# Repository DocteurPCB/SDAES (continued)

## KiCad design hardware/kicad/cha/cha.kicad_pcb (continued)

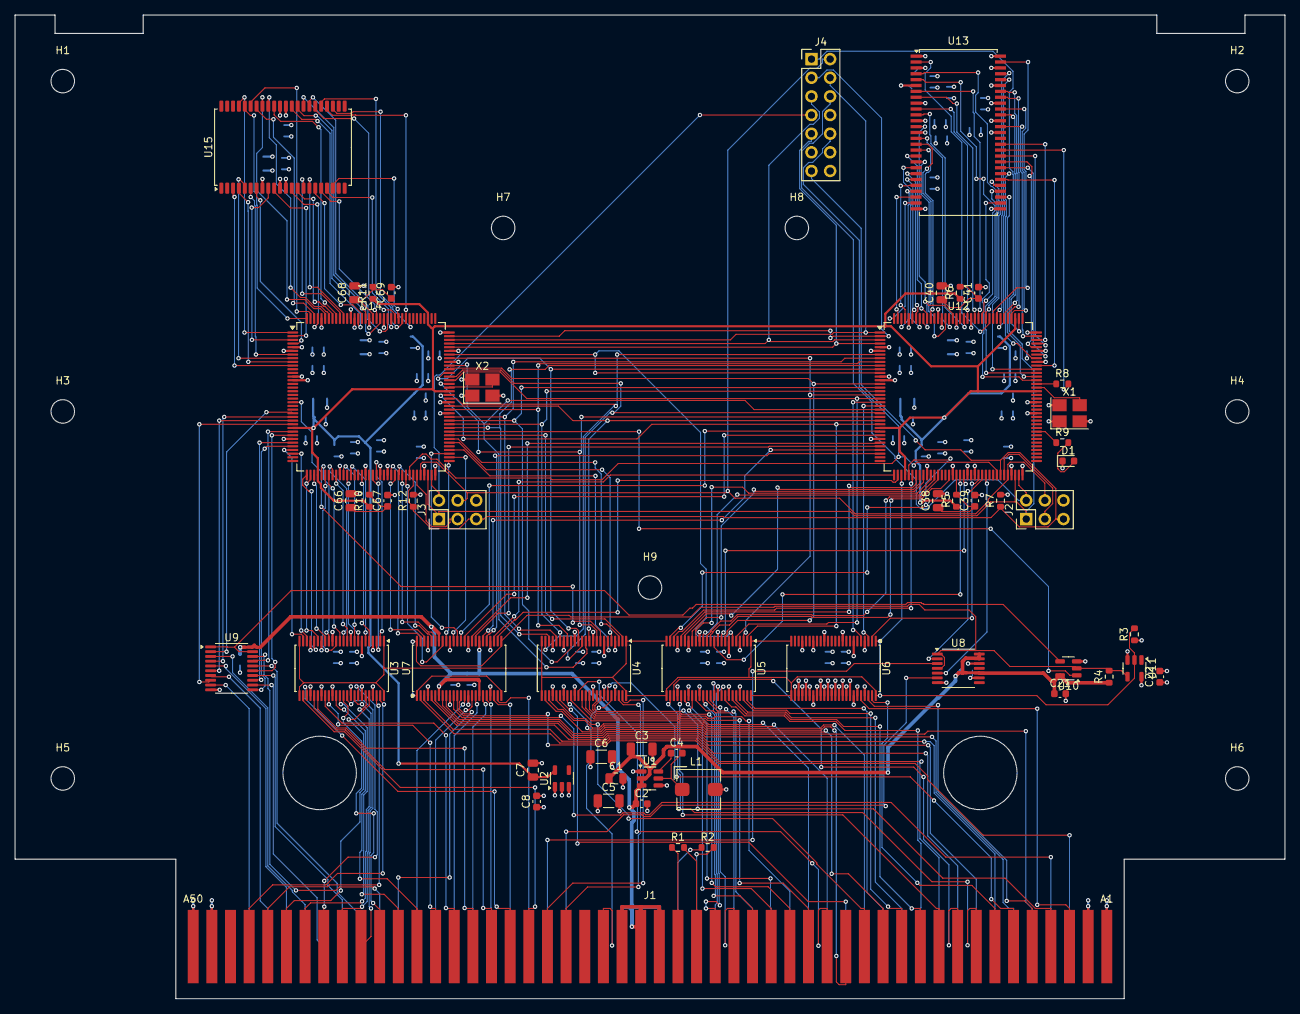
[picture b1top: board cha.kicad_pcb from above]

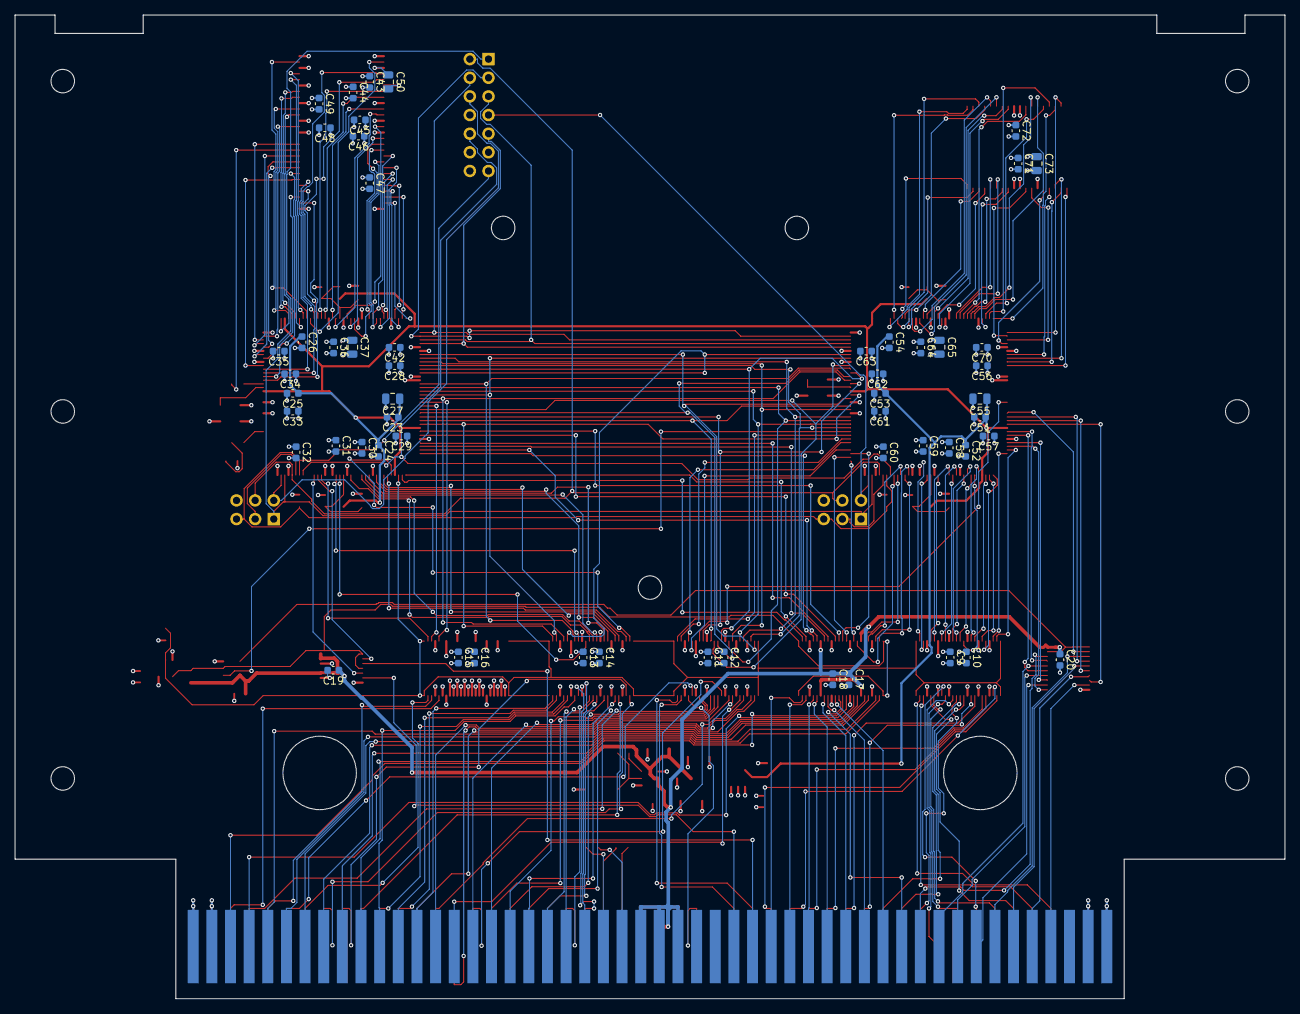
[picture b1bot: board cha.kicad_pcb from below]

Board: 4 copper layers, 173.0 x 134.0 mm, 117 parts (55 on the bottom side), 258 nets.

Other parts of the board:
H1, H2, H3, H4, H5, H6, H7, H8, H9: Entretoise M3; MountingHole_3.2mm_M3

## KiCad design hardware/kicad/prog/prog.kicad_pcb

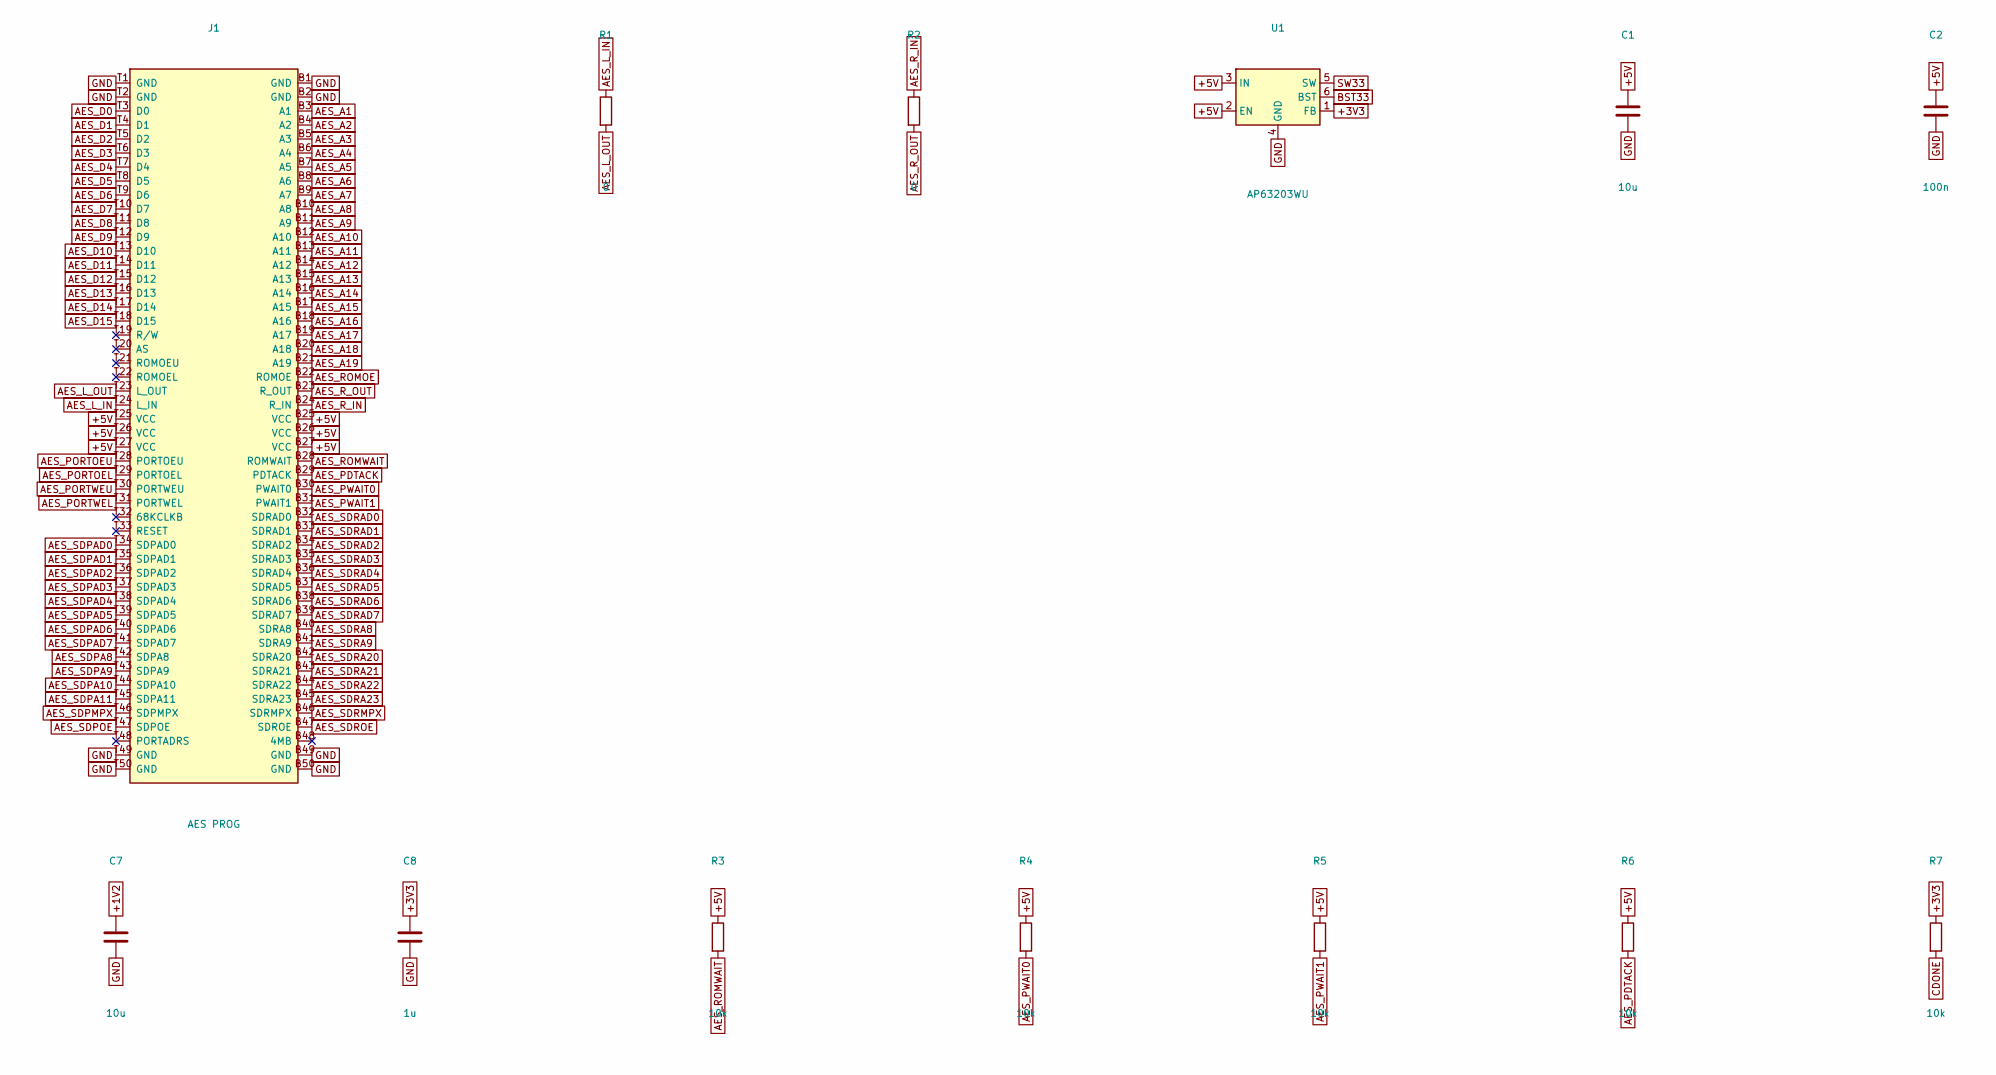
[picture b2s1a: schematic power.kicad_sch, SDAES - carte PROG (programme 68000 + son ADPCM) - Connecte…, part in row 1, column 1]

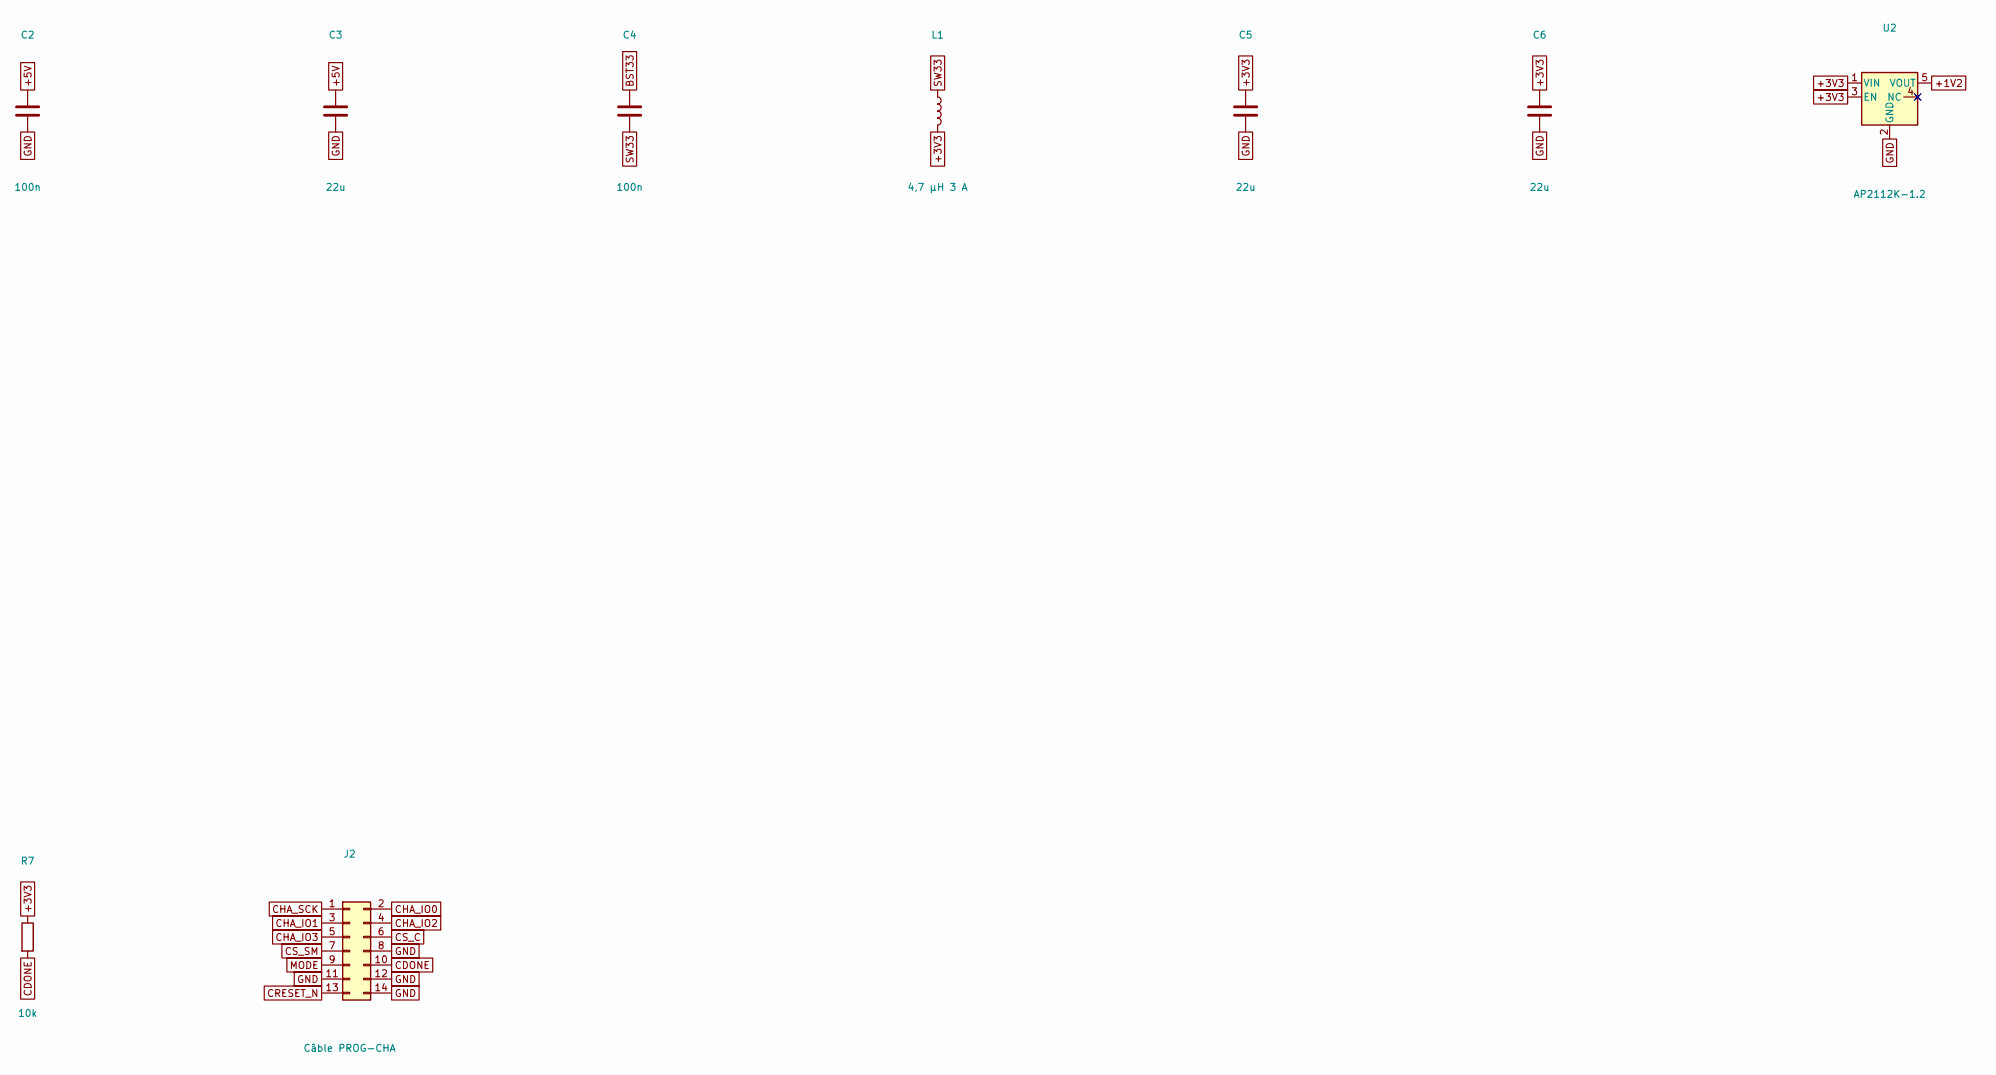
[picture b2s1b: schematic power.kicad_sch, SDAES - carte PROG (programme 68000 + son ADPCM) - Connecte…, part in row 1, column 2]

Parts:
C1, C7: 10u; C_0805_2012Metric
C2, C4: 100n; C_0603_1608Metric
C3, C5, C6: 22u; C_1206_3216Metric
C8: 1u; C_0603_1608Metric
J1: AES PROG; AES_Edge_2x50_P2.54mm
J2: Câble PROG-CHA; PinHeader_2x07_P2.54mm_Vertical
L1: 4,7 µH 3 A; L_Bourns_SRP5030T
R1, R2: 0; R_0603_1608Metric
R3, R4, R5, R6, R7: 10k; R_0603_1608Metric
U1: AP63203WU; TSOT-23-6
U2: AP2112K-1.2; SOT-23-5

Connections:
+1V2: C7.1, U2.5 (VOUT); also elsewhere on the board
+3V3: C5.1, C6.1, C8.1, L1.2, R7.1, U1.1 (FB), U2.1 (VIN), U2.3 (EN); also elsewhere on the board
+5V: C1.1, C2.1, C3.1, J1.B25 (VCC), J1.B26 (VCC), J1.B27 (VCC), J1.T25 (VCC), J1.T26 (VCC), J1.T27 (VCC), R3.1, R4.1, R5.1, R6.1, U1.2 (EN), U1.3 (IN); also elsewhere on the board
AES_A1: J1.B3 (A1); also elsewhere on the board
AES_A2: J1.B4 (A2); also elsewhere on the board
AES_A3: J1.B5 (A3); also elsewhere on the board
AES_A4: J1.B6 (A4); also elsewhere on the board
AES_A5: J1.B7 (A5); also elsewhere on the board
AES_A6: J1.B8 (A6); also elsewhere on the board
AES_A7: J1.B9 (A7); also elsewhere on the board
AES_A8: J1.B10 (A8); also elsewhere on the board
AES_A9: J1.B11 (A9); also elsewhere on the board
AES_A10: J1.B12 (A10); also elsewhere on the board
AES_A11: J1.B13 (A11); also elsewhere on the board
AES_A12: J1.B14 (A12); also elsewhere on the board
AES_A13: J1.B15 (A13); also elsewhere on the board
AES_A14: J1.B16 (A14); also elsewhere on the board
AES_A15: J1.B17 (A15); also elsewhere on the board
AES_A16: J1.B18 (A16); also elsewhere on the board
AES_A17: J1.B19 (A17); also elsewhere on the board
AES_A18: J1.B20 (A18); also elsewhere on the board
AES_A19: J1.B21 (A19); also elsewhere on the board
AES_D0: J1.T3 (D0); also elsewhere on the board
AES_D1: J1.T4 (D1); also elsewhere on the board
AES_D2: J1.T5 (D2); also elsewhere on the board
AES_D3: J1.T6 (D3); also elsewhere on the board
AES_D4: J1.T7 (D4); also elsewhere on the board
AES_D5: J1.T8 (D5); also elsewhere on the board
AES_D6: J1.T9 (D6); also elsewhere on the board
AES_D7: J1.T10 (D7); also elsewhere on the board
AES_D8: J1.T11 (D8); also elsewhere on the board
AES_D9: J1.T12 (D9); also elsewhere on the board
AES_D10: J1.T13 (D10); also elsewhere on the board
AES_D11: J1.T14 (D11); also elsewhere on the board
AES_D12: J1.T15 (D12); also elsewhere on the board
AES_D13: J1.T16 (D13); also elsewhere on the board
AES_D14: J1.T17 (D14); also elsewhere on the board
AES_D15: J1.T18 (D15); also elsewhere on the board
AES_L_IN: J1.T24 (L_IN), R1.1
AES_L_OUT: J1.T23 (L_OUT), R1.2
AES_PDTACK: J1.B29 (PDTACK), R6.2
AES_PORTOEL: J1.T29 (PORTOEL); also elsewhere on the board
AES_PORTOEU: J1.T28 (PORTOEU); also elsewhere on the board
AES_PORTWEL: J1.T31 (PORTWEL); also elsewhere on the board
AES_PORTWEU: J1.T30 (PORTWEU); also elsewhere on the board
AES_PWAIT0: J1.B30 (PWAIT0), R4.2; also elsewhere on the board
AES_PWAIT1: J1.B31 (PWAIT1), R5.2; also elsewhere on the board
AES_ROMOE: J1.B22 (ROMOE); also elsewhere on the board
AES_ROMWAIT: J1.B28 (ROMWAIT), R3.2; also elsewhere on the board
AES_R_IN: J1.B24 (R_IN), R2.1
AES_R_OUT: J1.B23 (R_OUT), R2.2
AES_SDPA8: J1.T42 (SDPA8); also elsewhere on the board
AES_SDPA9: J1.T43 (SDPA9); also elsewhere on the board
AES_SDPA10: J1.T44 (SDPA10); also elsewhere on the board
AES_SDPA11: J1.T45 (SDPA11); also elsewhere on the board
AES_SDPAD0: J1.T34 (SDPAD0); also elsewhere on the board
AES_SDPAD1: J1.T35 (SDPAD1); also elsewhere on the board
AES_SDPAD2: J1.T36 (SDPAD2); also elsewhere on the board
AES_SDPAD3: J1.T37 (SDPAD3); also elsewhere on the board
AES_SDPAD4: J1.T38 (SDPAD4); also elsewhere on the board
AES_SDPAD5: J1.T39 (SDPAD5); also elsewhere on the board
AES_SDPAD6: J1.T40 (SDPAD6); also elsewhere on the board
AES_SDPAD7: J1.T41 (SDPAD7); also elsewhere on the board
AES_SDPMPX: J1.T46 (SDPMPX); also elsewhere on the board
AES_SDPOE: J1.T47 (SDPOE); also elsewhere on the board
AES_SDRA8: J1.B40 (SDRA8); also elsewhere on the board
AES_SDRA9: J1.B41 (SDRA9); also elsewhere on the board
AES_SDRA20: J1.B42 (SDRA20); also elsewhere on the board
AES_SDRA21: J1.B43 (SDRA21); also elsewhere on the board
AES_SDRA22: J1.B44 (SDRA22); also elsewhere on the board
AES_SDRA23: J1.B45 (SDRA23); also elsewhere on the board
AES_SDRAD0: J1.B32 (SDRAD0); also elsewhere on the board
AES_SDRAD1: J1.B33 (SDRAD1); also elsewhere on the board
AES_SDRAD2: J1.B34 (SDRAD2); also elsewhere on the board
AES_SDRAD3: J1.B35 (SDRAD3); also elsewhere on the board
AES_SDRAD4: J1.B36 (SDRAD4); also elsewhere on the board
AES_SDRAD5: J1.B37 (SDRAD5); also elsewhere on the board
AES_SDRAD6: J1.B38 (SDRAD6); also elsewhere on the board
AES_SDRAD7: J1.B39 (SDRAD7); also elsewhere on the board
AES_SDRMPX: J1.B46 (SDRMPX); also elsewhere on the board
AES_SDROE: J1.B47 (SDROE); also elsewhere on the board
BST33: C4.1, U1.6 (BST)
CDONE: J2.10, R7.2; also elsewhere on the board
CHA_IO0: J2.2; also elsewhere on the board
CHA_IO1: J2.3; also elsewhere on the board
CHA_IO2: J2.4; also elsewhere on the board
CHA_IO3: J2.5; also elsewhere on the board
CHA_SCK: J2.1; also elsewhere on the board
CRESET_N: J2.13; also elsewhere on the board
CS_C: J2.6; also elsewhere on the board
CS_SM: J2.7; also elsewhere on the board
GND: C1.2, C2.2, C3.2, C5.2, C6.2, C7.2, C8.2, J1.B1 (GND), J1.B2 (GND), J1.B49 (GND), J1.B50 (GND), J1.T1 (GND), J1.T2 (GND), J1.T49 (GND), J1.T50 (GND), J2.8, J2.11, J2.12, J2.14, U1.4 (GND), U2.2 (GND); also elsewhere on the board
MODE: J2.9; also elsewhere on the board
SW33: C4.2, L1.1, U1.5 (SW)

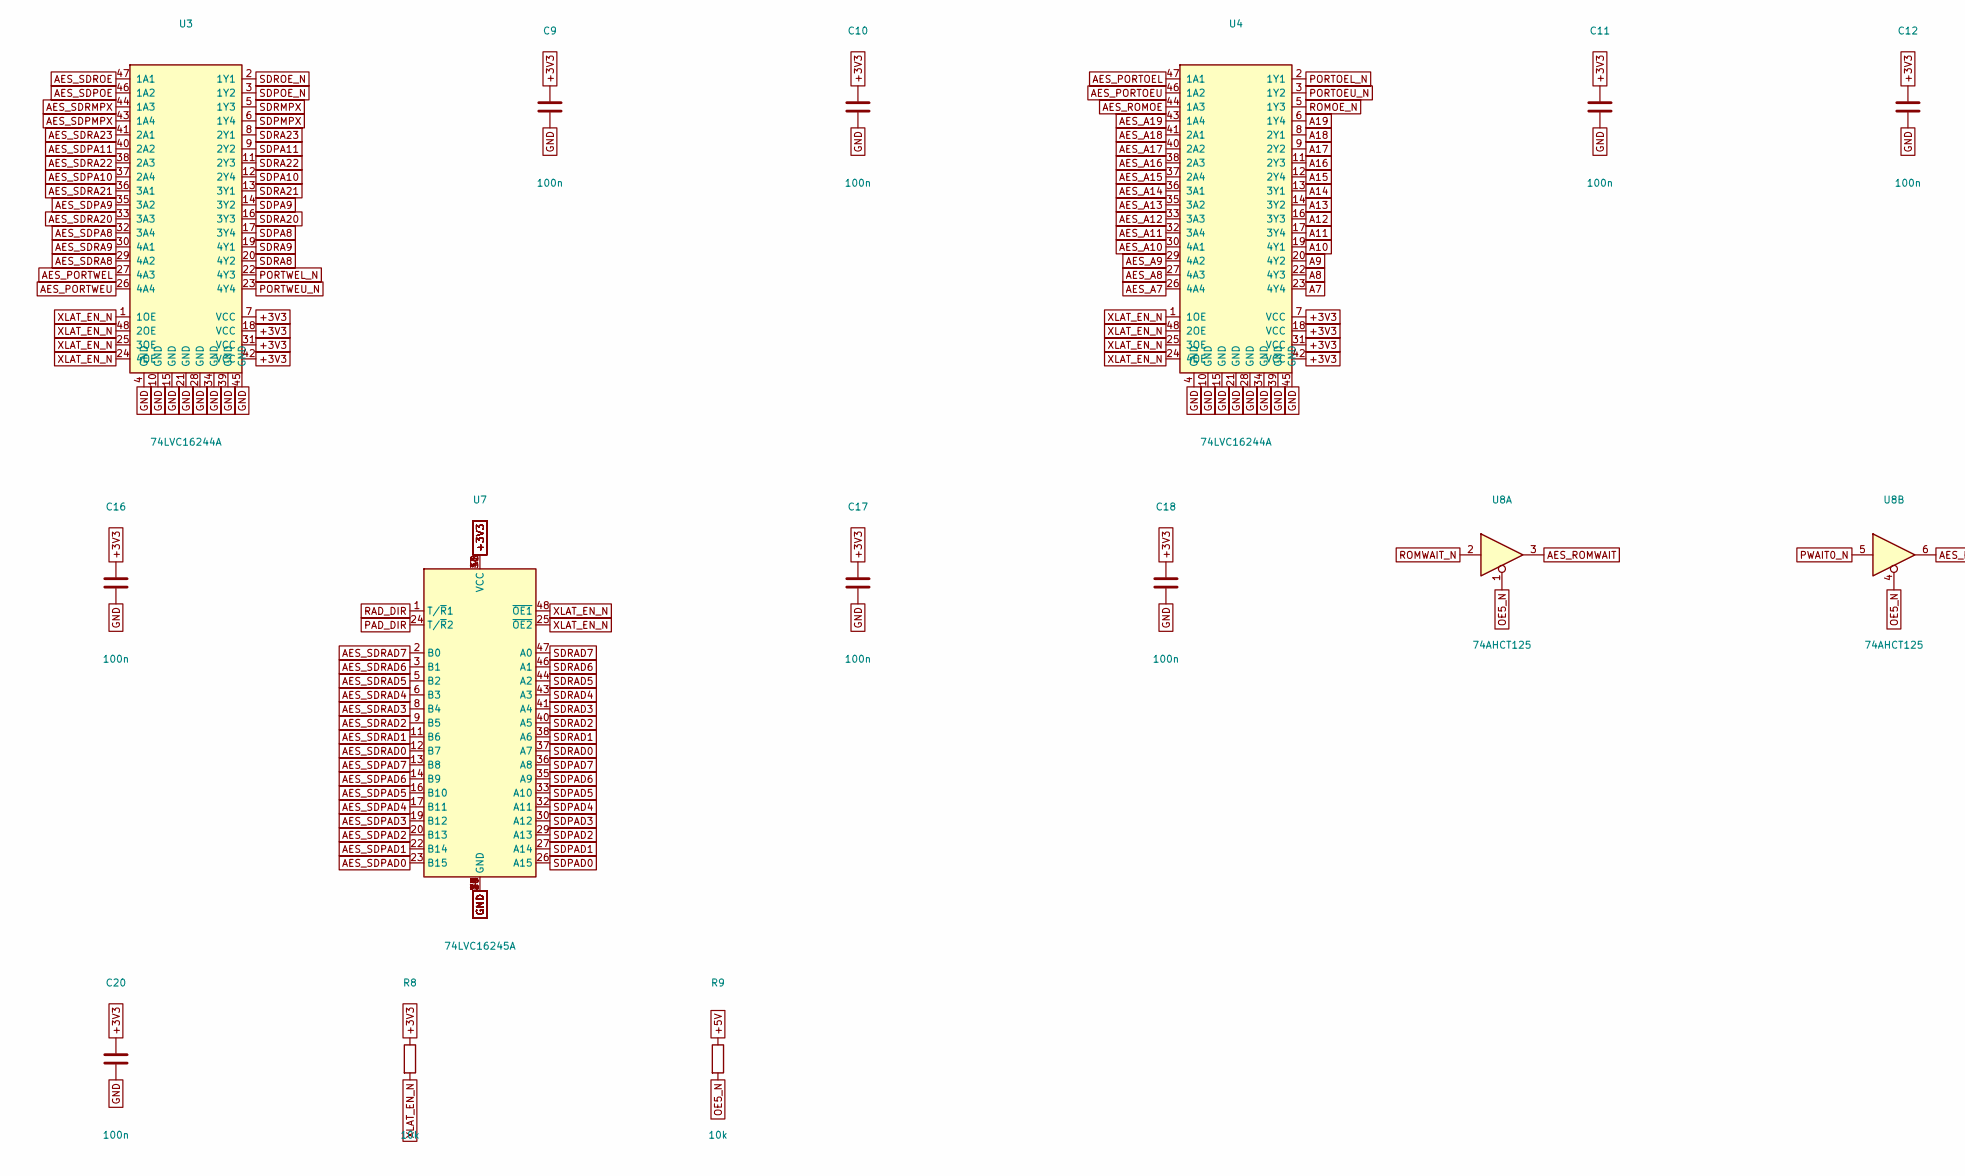
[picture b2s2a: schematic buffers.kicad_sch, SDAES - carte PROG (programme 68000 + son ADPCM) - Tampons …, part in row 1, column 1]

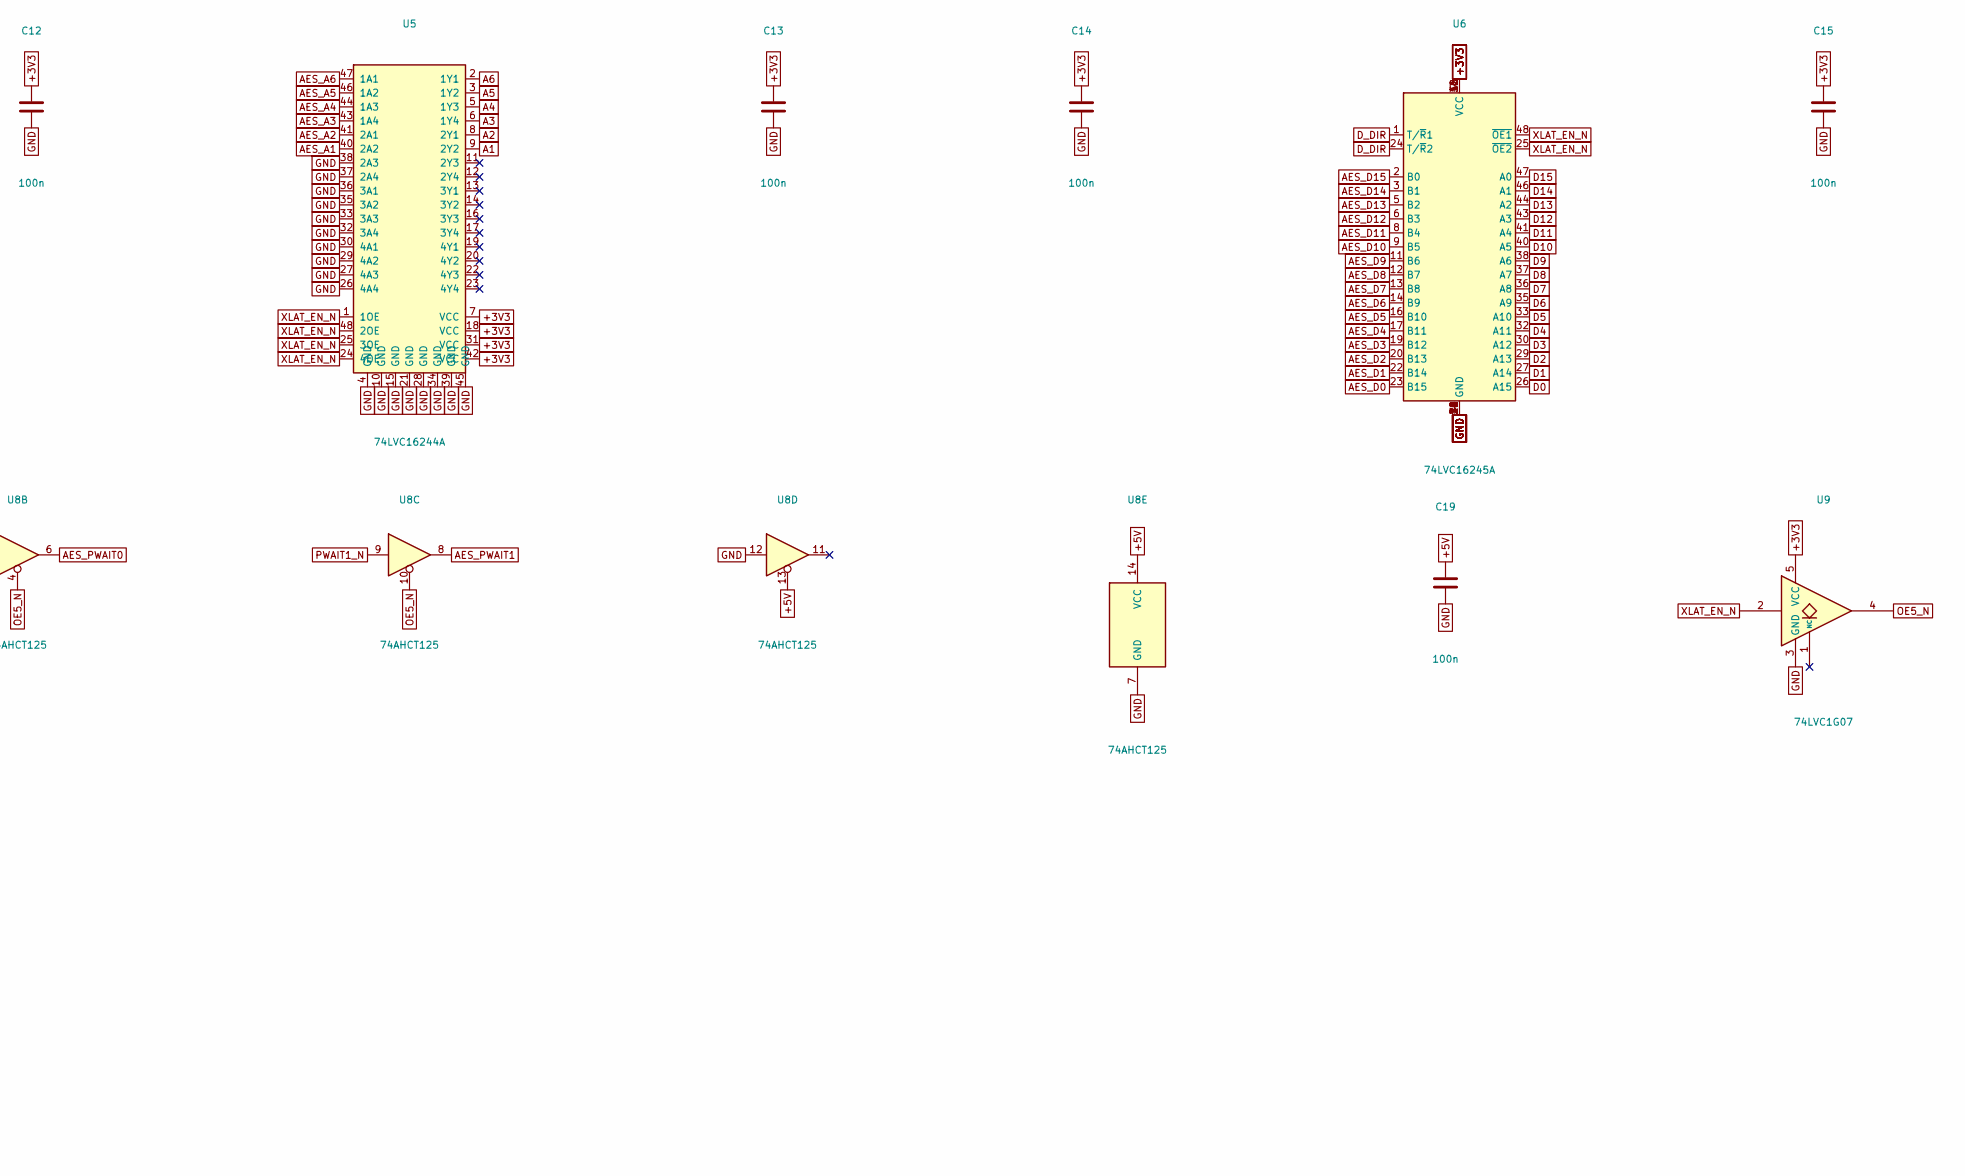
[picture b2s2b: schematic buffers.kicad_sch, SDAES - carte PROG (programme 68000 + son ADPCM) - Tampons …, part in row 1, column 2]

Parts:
C9, C10, C11, C12, C13, C14, C15, C16, C17, C18, C19, C20: 100n; C_0603_1608Metric
R8, R9: 10k; R_0603_1608Metric
U3, U4, U5: 74LVC16244A; TSSOP-48_6.1x12.5mm_P0.5mm
U6, U7: 74LVC16245A; TSSOP-48_6.1x12.5mm_P0.5mm
U8: 74AHCT125; TSSOP-14_4.4x5mm_P0.65mm
U9: 74LVC1G07; SOT-23-5

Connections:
+3V3: C9.1, C10.1, C11.1, C12.1, C13.1, C14.1, C15.1, C16.1, C17.1, C18.1, C20.1, R8.1, U3.7 (VCC), U3.18 (VCC), U3.31 (VCC), U3.42 (VCC), U4.7 (VCC), U4.18 (VCC), U4.31 (VCC), U4.42 (VCC), U5.7 (VCC), U5.18 (VCC), U5.31 (VCC), U5.42 (VCC), U6.7 (VCC), U6.18 (VCC), U6.31 (VCC), U6.42 (VCC), U7.7 (VCC), U7.18 (VCC), U7.31 (VCC), U7.42 (VCC), U9.5 (VCC); also elsewhere on the board
+5V: C19.1, R9.1, U8.13, U8.14 (VCC); also elsewhere on the board
A1: U5.9 (2Y2); also elsewhere on the board
A2: U5.8 (2Y1); also elsewhere on the board
A3: U5.6 (1Y4); also elsewhere on the board
A4: U5.5 (1Y3); also elsewhere on the board
A5: U5.3 (1Y2); also elsewhere on the board
A6: U5.2 (1Y1); also elsewhere on the board
A7: U4.23 (4Y4); also elsewhere on the board
A8: U4.22 (4Y3); also elsewhere on the board
A9: U4.20 (4Y2); also elsewhere on the board
A10: U4.19 (4Y1); also elsewhere on the board
A11: U4.17 (3Y4); also elsewhere on the board
A12: U4.16 (3Y3); also elsewhere on the board
A13: U4.14 (3Y2); also elsewhere on the board
A14: U4.13 (3Y1); also elsewhere on the board
A15: U4.12 (2Y4); also elsewhere on the board
A16: U4.11 (2Y3); also elsewhere on the board
A17: U4.9 (2Y2); also elsewhere on the board
A18: U4.8 (2Y1); also elsewhere on the board
A19: U4.6 (1Y4); also elsewhere on the board
AES_A1: U5.40 (2A2); also elsewhere on the board
AES_A2: U5.41 (2A1); also elsewhere on the board
AES_A3: U5.43 (1A4); also elsewhere on the board
AES_A4: U5.44 (1A3); also elsewhere on the board
AES_A5: U5.46 (1A2); also elsewhere on the board
AES_A6: U5.47 (1A1); also elsewhere on the board
AES_A7: U4.26 (4A4); also elsewhere on the board
AES_A8: U4.27 (4A3); also elsewhere on the board
AES_A9: U4.29 (4A2); also elsewhere on the board
AES_A10: U4.30 (4A1); also elsewhere on the board
AES_A11: U4.32 (3A4); also elsewhere on the board
AES_A12: U4.33 (3A3); also elsewhere on the board
AES_A13: U4.35 (3A2); also elsewhere on the board
AES_A14: U4.36 (3A1); also elsewhere on the board
AES_A15: U4.37 (2A4); also elsewhere on the board
AES_A16: U4.38 (2A3); also elsewhere on the board
AES_A17: U4.40 (2A2); also elsewhere on the board
AES_A18: U4.41 (2A1); also elsewhere on the board
AES_A19: U4.43 (1A4); also elsewhere on the board
AES_D0: U6.23 (B15); also elsewhere on the board
AES_D1: U6.22 (B14); also elsewhere on the board
AES_D2: U6.20 (B13); also elsewhere on the board
AES_D3: U6.19 (B12); also elsewhere on the board
AES_D4: U6.17 (B11); also elsewhere on the board
AES_D5: U6.16 (B10); also elsewhere on the board
AES_D6: U6.14 (B9); also elsewhere on the board
AES_D7: U6.13 (B8); also elsewhere on the board
AES_D8: U6.12 (B7); also elsewhere on the board
AES_D9: U6.11 (B6); also elsewhere on the board
AES_D10: U6.9 (B5); also elsewhere on the board
AES_D11: U6.8 (B4); also elsewhere on the board
AES_D12: U6.6 (B3); also elsewhere on the board
AES_D13: U6.5 (B2); also elsewhere on the board
AES_D14: U6.3 (B1); also elsewhere on the board
AES_D15: U6.2 (B0); also elsewhere on the board
AES_PORTOEL: U4.47 (1A1); also elsewhere on the board
AES_PORTOEU: U4.46 (1A2); also elsewhere on the board
AES_PORTWEL: U3.27 (4A3); also elsewhere on the board
AES_PORTWEU: U3.26 (4A4); also elsewhere on the board
AES_PWAIT0: U8.6; also elsewhere on the board
AES_PWAIT1: U8.8; also elsewhere on the board
AES_ROMOE: U4.44 (1A3); also elsewhere on the board
AES_ROMWAIT: U8.3; also elsewhere on the board
AES_SDPA8: U3.32 (3A4); also elsewhere on the board
AES_SDPA9: U3.35 (3A2); also elsewhere on the board
AES_SDPA10: U3.37 (2A4); also elsewhere on the board
AES_SDPA11: U3.40 (2A2); also elsewhere on the board
AES_SDPAD0: U7.23 (B15); also elsewhere on the board
AES_SDPAD1: U7.22 (B14); also elsewhere on the board
AES_SDPAD2: U7.20 (B13); also elsewhere on the board
AES_SDPAD3: U7.19 (B12); also elsewhere on the board
AES_SDPAD4: U7.17 (B11); also elsewhere on the board
AES_SDPAD5: U7.16 (B10); also elsewhere on the board
AES_SDPAD6: U7.14 (B9); also elsewhere on the board
AES_SDPAD7: U7.13 (B8); also elsewhere on the board
AES_SDPMPX: U3.43 (1A4); also elsewhere on the board
AES_SDPOE: U3.46 (1A2); also elsewhere on the board
AES_SDRA8: U3.29 (4A2); also elsewhere on the board
AES_SDRA9: U3.30 (4A1); also elsewhere on the board
AES_SDRA20: U3.33 (3A3); also elsewhere on the board
AES_SDRA21: U3.36 (3A1); also elsewhere on the board
AES_SDRA22: U3.38 (2A3); also elsewhere on the board
AES_SDRA23: U3.41 (2A1); also elsewhere on the board
AES_SDRAD0: U7.12 (B7); also elsewhere on the board
AES_SDRAD1: U7.11 (B6); also elsewhere on the board
AES_SDRAD2: U7.9 (B5); also elsewhere on the board
AES_SDRAD3: U7.8 (B4); also elsewhere on the board
AES_SDRAD4: U7.6 (B3); also elsewhere on the board
AES_SDRAD5: U7.5 (B2); also elsewhere on the board
AES_SDRAD6: U7.3 (B1); also elsewhere on the board
AES_SDRAD7: U7.2 (B0); also elsewhere on the board
AES_SDRMPX: U3.44 (1A3); also elsewhere on the board
AES_SDROE: U3.47 (1A1); also elsewhere on the board
D0: U6.26 (A15); also elsewhere on the board
D1: U6.27 (A14); also elsewhere on the board
D2: U6.29 (A13); also elsewhere on the board
D3: U6.30 (A12); also elsewhere on the board
D4: U6.32 (A11); also elsewhere on the board
D5: U6.33 (A10); also elsewhere on the board
D6: U6.35 (A9); also elsewhere on the board
D7: U6.36 (A8); also elsewhere on the board
D8: U6.37 (A7); also elsewhere on the board
D9: U6.38 (A6); also elsewhere on the board
D10: U6.40 (A5); also elsewhere on the board
D11: U6.41 (A4); also elsewhere on the board
D12: U6.43 (A3); also elsewhere on the board
D13: U6.44 (A2); also elsewhere on the board
D14: U6.46 (A1); also elsewhere on the board
D15: U6.47 (A0); also elsewhere on the board
D_DIR: U6.1 (T/~R1), U6.24 (T/~R2); also elsewhere on the board
GND: C9.2, C10.2, C11.2, C12.2, C13.2, C14.2, C15.2, C16.2, C17.2, C18.2, C19.2, C20.2, U3.4 (GND), U3.10 (GND), U3.15 (GND), U3.21 (GND), U3.28 (GND), U3.34 (GND), U3.39 (GND), U3.45 (GND), U4.4 (GND), U4.10 (GND), U4.15 (GND), U4.21 (GND), U4.28 (GND), U4.34 (GND), U4.39 (GND), U4.45 (GND), U5.4 (GND), U5.10 (GND), U5.15 (GND), U5.21 (GND), U5.26 (4A4), U5.27 (4A3), U5.28 (GND), U5.29 (4A2), U5.30 (4A1), U5.32 (3A4), U5.33 (3A3), U5.34 (GND), U5.35 (3A2), U5.36 (3A1), U5.37 (2A4), U5.38 (2A3), U5.39 (GND), U5.45 (GND), U6.4 (GND), U6.10 (GND), U6.15 (GND), U6.21 (GND), U6.28 (GND), U6.34 (GND), U6.39 (GND), U6.45 (GND), U7.4 (GND), U7.10 (GND), U7.15 (GND), U7.21 (GND), U7.28 (GND), U7.34 (GND), U7.39 (GND), U7.45 (GND), U8.7 (GND), U8.12, U9.3 (GND); also elsewhere on the board
OE5_N: R9.2, U8.1, U8.4, U8.10, U9.4
PAD_DIR: U7.24 (T/~R2); also elsewhere on the board
PORTOEL_N: U4.2 (1Y1); also elsewhere on the board
PORTOEU_N: U4.3 (1Y2); also elsewhere on the board
PORTWEL_N: U3.22 (4Y3); also elsewhere on the board
PORTWEU_N: U3.23 (4Y4); also elsewhere on the board
PWAIT0_N: U8.5; also elsewhere on the board
PWAIT1_N: U8.9; also elsewhere on the board
RAD_DIR: U7.1 (T/~R1); also elsewhere on the board
ROMOE_N: U4.5 (1Y3); also elsewhere on the board
ROMWAIT_N: U8.2; also elsewhere on the board
SDPA8: U3.17 (3Y4); also elsewhere on the board
SDPA9: U3.14 (3Y2); also elsewhere on the board
SDPA10: U3.12 (2Y4); also elsewhere on the board
SDPA11: U3.9 (2Y2); also elsewhere on the board
SDPAD0: U7.26 (A15); also elsewhere on the board
SDPAD1: U7.27 (A14); also elsewhere on the board
SDPAD2: U7.29 (A13); also elsewhere on the board
SDPAD3: U7.30 (A12); also elsewhere on the board
SDPAD4: U7.32 (A11); also elsewhere on the board
SDPAD5: U7.33 (A10); also elsewhere on the board
SDPAD6: U7.35 (A9); also elsewhere on the board
SDPAD7: U7.36 (A8); also elsewhere on the board
SDPMPX: U3.6 (1Y4); also elsewhere on the board
SDPOE_N: U3.3 (1Y2); also elsewhere on the board
SDRA8: U3.20 (4Y2); also elsewhere on the board
SDRA9: U3.19 (4Y1); also elsewhere on the board
SDRA20: U3.16 (3Y3); also elsewhere on the board
SDRA21: U3.13 (3Y1); also elsewhere on the board
SDRA22: U3.11 (2Y3); also elsewhere on the board
SDRA23: U3.8 (2Y1); also elsewhere on the board
SDRAD0: U7.37 (A7); also elsewhere on the board
SDRAD1: U7.38 (A6); also elsewhere on the board
SDRAD2: U7.40 (A5); also elsewhere on the board
SDRAD3: U7.41 (A4); also elsewhere on the board
SDRAD4: U7.43 (A3); also elsewhere on the board
SDRAD5: U7.44 (A2); also elsewhere on the board
SDRAD6: U7.46 (A1); also elsewhere on the board
SDRAD7: U7.47 (A0); also elsewhere on the board
SDRMPX: U3.5 (1Y3); also elsewhere on the board
SDROE_N: U3.2 (1Y1); also elsewhere on the board
XLAT_EN_N: R8.2, U3.1 (1OE), U3.24 (4OE), U3.25 (3OE), U3.48 (2OE), U4.1 (1OE), U4.24 (4OE), U4.25 (3OE), U4.48 (2OE), U5.1 (1OE), U5.24 (4OE), U5.25 (3OE), U5.48 (2OE), U6.25 (~OE2), U6.48 (~OE1), U7.25 (~OE2), U7.48 (~OE1), U9.2; also elsewhere on the board
